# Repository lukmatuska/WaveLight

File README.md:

# WaveLight

A gesture-controlled night light. Wave your hand over it to turn it on or off,
hold your hand over it to set the flame size, and double-wave to pick a color.
The light is an animated candle flame on WS2812 LEDs. It runs on a Li-ion
battery and sleeps when nobody is around.

- **MCU:** ATtiny416 (4 kB flash, 256 B RAM), internal 16 MHz oscillator
- **Sensor:** ams TMF8801 time-of-flight distance sensor
- **LEDs:** 4× WS2812B-2020 (count is configurable)
- **Firmware:** C, MPLAB XC8 (free license), in [`FW/`](FW/)
- **Hardware:** KiCad project in the repository root

---

## Using it

| Gesture | What it does |
|---|---|
| **Wave** (hand over the sensor and away again, under 0.6 s) | Light on / off. Reacts ~0.5 s after the hand leaves, because it waits to see if a second wave follows |
| **Hold + move** (hand stays over the sensor, then moves) | Flame size: closer = smaller, dimmer embers; farther = bigger, brighter flame. Saved when the hand leaves |
| **Wave, then hold right away** | Turns on, then sets the flame size |
| **Double wave** | Color mode: the light dips briefly. Bring your hand back within 2 s and the color follows its distance. Take the hand away, and after 1 s the light dips again and the color is saved |

**Distances:** hands are detected up to **60 cm**. Size and color are set
between about **6 cm** (closest) and **32 cm** (farthest).

**Colors**, from close to far in color mode:

| Hand distance | ~6 cm | | | | | | | | | ~32 cm |
|---|---|---|---|---|---|---|---|---|---|---|
| Color | red | orange | yellow | green | cyan | blue | magenta | red | warm white (2700 K) | cool white (6500 K) |

So the strip goes once around the color wheel back to red, then into warm
white and cools down to 6500 K. The hotter parts of the flame shift a little
further along the strip, which gives the flame its lighter tips.

### Status signals

| LEDs | Meaning |
|---|---|
| Brief dip to dark and back | Color mode started / ended |
| Magenta for 1 s at power-on | Sensor calibrated and calibration stored (first boot after flashing) |
| Red blinking continuously | Sensor not responding. Retries every ~8 s (watchdog reset) |
| 2 red blinks when turning on | Battery low (< 3.5 V), turns on anyway |
| 3 red blinks, stays off | Battery critical (< 3.3 V). Charge above 3.5 V to use again |

The battery signals only appear if the battery check is enabled (see
[Configuration](#configuration)).

### Things that might surprise you

- **Static objects are learned.** Anything that stays still for 10 s becomes
  background. A hand only counts if it is at least 8 cm closer than the
  background, so you can wave between the lamp and e.g. a shelf. After you
  place or remove something, give it ~10 s to adapt.
- **Placed objects never change the settings.** A hold only adjusts the flame
  once the hand has *moved* 3 cm, and objects don't move.
- **Pulling your hand away doesn't change the setting.** On release the
  value from ~200 ms earlier is kept.
- **Idle:** after 15 s without a hand, whether the light is on or off, the
  sensor slows down (one shorter measurement every 200 ms) to save power. The
  first wave still works, but a very quick flick can be missed. Idle
  measurements are shorter, so a hand near the 60 cm limit may only be
  noticed once it comes a bit closer.

---

## Hardware

### Pinout

| ATtiny416 pin | Function |
|---|---|
| PB3 | WS2812 data (LED strip connector J2; also gate of Q1 for the alternative power LED on J3) |
| PB1 / PB0 | I²C SDA / SCL to the TMF8801 (internal pull-ups, no external resistors fitted) |
| PC0 | TMF8801 INT (open drain, internal pull-up) - wakes the MCU |
| PC1 | TMF8801 EN |
| PB4 / PB2 | TMF8801 GPIO0 / GPIO1 (unused, driven low by the sensor) |
| PA1 | Battery voltage measurement (divider middle) |
| PC3 | Battery divider low side - pulled low only while measuring |
| PA0 | UPDI programming |

### Board

- **Power:** Li-ion battery (J6) → power switch (SW1) → TCR2L LDO → VDD for
  the MCU and sensor. The LED strip runs directly from the battery voltage.
- **Charging:** USB-C (J7) or the jack tip → charger IC (U3, charge current set
  by R3). The charger's battery output is on the switched side of SW1, so the
  battery only charges while the switch is on.
- **3.5 mm jack (J1):** tip = charger input, ring = UPDI, sleeve = GND. It is
  used for programming.
- **J4 / J5:** sensor signal headers (VDD, GPIO0/1, SDA, SCL, INT, EN, GND).
- **JP1:** solder jumper EN → GND (holds the sensor off when closed).
- **Battery divider:** R2 1 MΩ (battery → PA1) and R4 470 kΩ (PA1 → PC3).

### Known hardware limitations

- **No I²C pull-ups.** The internal ones are used and the bus runs at 50 kHz.
  Add 4.7 kΩ to VDD on SDA/SCL in the next revision.
- **The LEDs run straight from the battery.** The WS2812B-2020 is specified
  for 3.3-5.3 V. Below ~3.6 V the green and blue channels may lose current
  (dimmer, redder light), and below 3.3 V the LEDs are out of spec.
- **The sensor dominates standby current** (~3 mA), see
  [Power analysis](#power-analysis). A 300 mAh battery lasts about 3.5 days in
  standby.
- **Sensor range is ~64 cm** with the firmware built into the sensor (see
  [Sensor range](#sensor-range)).

---

## Firmware

### Files

| File | Contents |
|---|---|
| [`main.c`](FW/main.c) | Configuration, startup, main loop, gesture → action mapping, sleep, EEPROM settings |
| [`gesture.h`](FW/gesture.h) | Wave / double wave / hold / tracking detection, background learning |
| [`light.h`](FW/light.h) | Flame animation, colors, fades, gamma correction, auto-off |
| [`tmf8801.h`](FW/tmf8801.h) | TMF8801 driver: power-up, factory calibration, measurement, results |
| [`battery.h`](FW/battery.h) | Battery voltage check (ADC) |
| [`twi.h`](FW/twi.h) | I²C master driver |
| [`ws2812b.h`](FW/ws2812b.h) | Cycle-counted WS2812 driver (16 MHz) |
| [`PATCHING.md`](FW/PATCHING.md) | How to upload the TMF8801 RAM patch after switching to an ATtiny1616 |

### Building and flashing

1. Open `FW/` in VS Code with the MPLAB extensions (project file
   `FW/.vscode/Wavelight-firmware.mplab.json`, XC8 v3.00, `ATtiny_DFP` 3.4.278).
2. Build. The optimization level in the project doesn't matter: `main.c`
   forces `-O2` without inlining with a `#pragma`. At `-O0` the firmware
   doesn't fit. The free XC8 license allows `-O2` but not `-Os`.
3. Flash over UPDI (the project uses an MPLAB Snap).
4. **Set the fuse `OSCCFG` to 16 MHz** (`FREQSEL_16MHZ`) on every new chip.
   The factory default is 20 MHz, and then all timing (LED data, I²C, gestures)
   is off by 25%.
5. **First boot after flashing:** keep nothing within 40 cm of the sensor,
   ideally in the dark. The sensor calibrates itself and stores the result
   (1 s magenta flash).

Flashing erases the EEPROM, which holds the sensor calibration and the saved size
and color, unless the `EESAVE` fuse is set.

Flash usage is about 3.65 kB, or 3.9 kB with the battery check, out of 4 kB.

### Configuration

All settings are `#define`s.

**[`main.c`](FW/main.c)**

| Define | Default | Meaning |
|---|---|---|
| `DEBUG_DISTANCE` | 0 | 1 = show the raw distance on the LEDs instead of the night light (see [Debug mode](#debug-mode)) |
| `BATTERY_CHECK` | 0 | 1 = battery divider is fitted, enable the battery check |
| `LED_COUNT` | 4 | Number of WS2812 LEDs (~5 bytes RAM each, up to ~40) |
| `TICK_MS` | 10 | Main loop period |
| `ADJUST_NEAR_MM` | 60 | Hand distance for the smallest flame / first color. +1 step per mm up to 255 steps (~32 cm) |
| `TONE_MODE_WAIT_MS` | 2000 | Time to bring the hand back after a double wave |
| `TONE_MODE_END_MS` | 1000 | Color mode ends this long after the hand left |
| `BATTERY_PERIOD_MS` | 60000 | Battery check interval while running |
| `SENSOR_ACTIVE_MS` | 33 | Sensor measurement period while a hand is around |
| `SENSOR_ACTIVE_KITER` | 900 | Sensor iterations (thousands) per measurement while active |
| `SENSOR_IDLE_MS` | 200 | Sensor measurement period while idle (max 255). Longer = less power, more missed flicks |
| `SENSOR_IDLE_KITER` | 600 | Iterations while idle. Fewer = less power per measurement, maybe less range |
| `IDLE_AFTER_MS` | 15000 | No hand this long → sensor idle (light on or off) |

**[`gesture.h`](FW/gesture.h)**

| Define | Default | Meaning |
|---|---|---|
| `GESTURE_NEAR_MM` | 600 | Maximum hand distance |
| `GESTURE_DROPOUT` | 2 | Missed readings in a row before a hand counts as gone (bridges glitches near the range limit) |
| `GESTURE_BG_MARGIN_MM` | 80 | A hand must be this much closer than the background |
| `GESTURE_BG_TOL_MM` | 30 | Readings within this count as "not moving" |
| `GESTURE_BG_LEARN_MS` | 10000 | Static this long → becomes background |
| `GESTURE_WAVE_MIN_MS` | 50 | Shorter presence = noise |
| `GESTURE_WAVE_MAX_MS` | 600 | Longer presence = hold. Raise it if your waves are slow |
| `GESTURE_DOUBLE_GAP_MS` | 500 | Maximum pause between the two waves of a double wave |
| `GESTURE_HOLD_MOVE_MM` | 30 | A hold only adjusts after the hand moved this much |
| `GESTURE_HISTORY` | 6 | Readings (~200 ms) rolled back when the hand leaves |

**[`light.h`](FW/light.h)**

| Define | Default | Meaning |
|---|---|---|
| `LIGHT_FADE_ON_MS` / `LIGHT_FADE_OFF_MS` | 800 / 1500 | Fade times |
| `LIGHT_AUTO_OFF_MIN` | 0 | Turn off after this many minutes, 0 = never |
| `LIGHT_DEFAULT_BRIGHTNESS` | 255 | Flame size before anything is saved |
| `LIGHT_MIN_BRIGHTNESS` | 24 | Smallest flame size |
| `LIGHT_DEFAULT_TONE` | 0 | Color before anything is saved (0 = red-orange flame). ~10 gives a more orange flame |
| `LIGHT_WB_G` / `LIGHT_WB_B` | 176 / 240 | White balance: WS2812 green and blue are much stronger than red. Tune until the 4000 K white looks neutral |
| `FLAME_SPREAD` | 110 | How much the flame flickers above its base heat |
| `FLAME_CHANGE` | 40 | How often the flicker changes (chance per tick, of 256) |
| `FLAME_GUST` | 2 | How often the whole flame dips (chance per tick, of 256) |
| `FLAME_SPEED` | 2 | Smoothing; higher = calmer flame |
| `FLAME_HUE_SHIFT` | 24 | How much hotter parts shift along the color strip |
| `LIGHT_WHEEL_END` | 192 | Where the color wheel ends and the white strip starts |

**[`battery.h`](FW/battery.h)**

| Define | Default | Meaning |
|---|---|---|
| `BATTERY_LOW_MV` | 3500 | Warn when turning on |
| `BATTERY_CRITICAL_MV` | 3300 | Refuse to turn on / turn off. Cleared above `BATTERY_LOW_MV` |
| `BATTERY_R_TOP` / `BATTERY_R_BOTTOM` | 1000 / 470 | Divider resistors in kΩ |

### How it works

**Sensor.** The TMF8801 runs the measurement app built into its ROM. No
firmware is uploaded, because the ~11 kB patch doesn't fit in 4 kB.
On the first boot the sensor runs its factory calibration (crosstalk). The
14-byte result is stored in EEPROM and sent to the sensor on every start.
It measures with 900k iterations; each measurement takes ~27 ms.

**Gestures.** Every sensor result goes into `gesture_reading()`, which
decides whether a hand is present. `gesture_update()` runs every 10 ms and
turns presence over time into events: wave, double wave, hold, hold end,
track, track end. While color mode is active, wave and hold detection are off
and the hand position is reported directly ("tracking"). When color mode ends,
a hand that is still there is ignored until it leaves, so color mode never
turns into a size change.

**Light.** The output level fades linearly in perceptual brightness and is
gamma-corrected, so fades look even. Each LED has a "heat" value that
drifts towards random targets. Neighboring LEDs are coupled, so the flicker
travels along the strip, and occasionally the whole flame dips (a gust).
Heat sets both the brightness and a small color shift. The size setting moves
the base heat up and down.

**Power.** While a hand is around, the sensor measures every 33 ms with 900k
iterations. After `IDLE_AFTER_MS` with no hand, no gesture pending and no
color mode, **whether the light is on or off**, the sensor switches to
`SENSOR_IDLE_MS` / `SENSOR_IDLE_KITER` (200 ms, 600k) and goes to standby
between measurements. A hand switches it back.

What the MCU does then depends on the light:
- **Light on (or fading):** the MCU stays awake and runs the flame every 10 ms.
- **Light off:** the MCU goes to power-down and is woken by the sensor's INT
  pin, which goes low on every result (the TMF8801 has no distance-threshold
  interrupt). After each wake, the firmware catches up the missed 10 ms ticks
  so all timing stays correct, then sleeps again unless a hand was seen.

Unused pins have their digital inputs disabled, and the battery divider only
draws current during a measurement. A watchdog (~8 s, also running in sleep)
resets the device if the sensor ever stops waking it.

For the resulting currents and battery life, see [Power analysis](#power-analysis).

**Settings.** The flame size and color are saved to EEPROM when a hold or
color mode ends, and only if they changed. EEPROM layout: page 0 =
calibration + marker, page 1 = size, color + marker.

### Debug mode

Set `DEBUG_DISTANCE 1` to show what the sensor sees, at 10 cm resolution:

- **Color = 40 cm band:** green 0-40, yellow 40-80, red 80-120,
  magenta 120-160, white over 160 cm
- **Number of lit LEDs = 10 cm steps within the band** (1-4). For example,
  3 yellow = 60-70 cm.
- **First LED blue:** the sensor reports no object
- **All cyan:** no new reading for 0.5 s

The display assumes 4 LEDs.

### Sensor range

With the ROM firmware, the TMF8801 here reports "no object" beyond ~64 cm,
even for a white wall in the dark with calibration. The datasheet only
promises its 2.5 m range with the latest ams RAM patch (~11 kB, uploaded
on every boot) and a tuned oscillator. An ATtiny1616 (16 kB) in the same
package fits the patch. The steps are in [`FW/PATCHING.md`](FW/PATCHING.md).

---

## Power analysis

Estimates for 4× WS2812B-2020 and a **300 mAh** Li-ion battery. They are
calculated from datasheet values and a simulation of the flame code. **Nothing
has been measured yet.**

### Assumptions

- **Usable capacity 270 mAh:** about 90% of 300 mAh, from 4.2 V down to the
  3.3 V cut-off.
- **Battery current = load current.** The LDO is linear, and the LEDs are
  constant-current drivers. This holds while the battery is high enough for
  the green/blue LED channels (~3.6 V); below that the LEDs draw less and get
  dimmer.
- **Room temperature, typical (not maximum) values.**
- **Default firmware settings:** sensor every 33 ms with 900k iterations
  while a hand is around, every 200 ms with 600k iterations while idle; MCU at
  16 MHz.
- **The iteration count really changes the measurement time.** The datasheet
  contradicts itself on the byte order, and the firmware follows the register
  description. **Verify by measuring the standby current with
  `SENSOR_IDLE_KITER` 600 vs 900.** It should drop by about a third; if it
  doesn't, the byte order is wrong.

### Per component

| Component | State | Current | Source |
|---|---|---|---|
| TMF8801 | active: every 33 ms, 900k (hand around, or < 15 s after) | ~27 mA | DS000648: 27 mA average at 30 Hz, 900k iterations |
| TMF8801 | idle: every 200 ms, 600k | **~3.0 mA** | DS000648: 17.7 mA at 30 Hz with 600k → ~0.59 mC per measurement; + 85 µA standby in between |
| ATtiny416 | awake, 16 MHz, ~3 V (light on) | ~3 mA | datasheet fig. 36-1 |
| ATtiny416 | light off, idle: power-down + ~6 ms awake per wake-up (I²C, catch-up ticks) | ~0.1 mA | 3% of 3 mA; power-down itself ~0.2 µA (fig. 36-9) |
| WS2812B-2020 ×4 | dark | ≤ 4 µA | V6 datasheet: quiescent ≤ 1 µA each |
| WS2812B-2020 ×4 | flame | 3-71 mA average, see below | 12 mA per channel at full, flame simulated |
| LDO, charger, watchdog, divider, pull-ups | always | a few µA | negligible |

### LED current of the flame

These figures come from simulating the actual `light.h` algorithm (random
generator, heat model, colors, white balance) for 10 minutes. Each LED channel
draws 12 mA × PWM / 255.

| Color | Size 255 | Size 160 | Size 80 | Size 24 (min) |
|---|---|---|---|---|
| Red (default) | 31.5 mA | 15.6 mA | 6.9 mA | 3.1 mA |
| Orange | 44.4 mA | 21.3 mA | 9.1 mA | 4.0 mA |
| Yellow | 28.6 mA | 17.3 mA | 9.1 mA | 4.6 mA |
| Blue | 30.5 mA | 14.9 mA | 6.6 mA | 3.0 mA |
| Warm white 2700 K | 41.2 mA | 21.1 mA | 9.5 mA | 4.3 mA |
| Cool white 6500 K | 71.4 mA | 37.6 mA | 17.4 mA | 8.1 mA |

- **Peak:** about 108 mA for the LEDs (cool white, size 255, during flicker
  peaks), so ~140 mA in total. This is under 0.5 C for a 300 mAh cell.
- **Theoretical maximum:** 4 × 36 mA = 144 mA; the flame never gets there.

### Total current and run time (270 mAh usable)

After the first 15 s without a hand, the light runs with the sensor idle. The
"on" rows assume that; the active state only applies briefly after each
interaction.

| Scenario | Sensor | MCU | LEDs | Total | Run time |
|---|---|---|---|---|---|
| **Standby** (light off, idle) | 3.0 | 0.1 | 0 | **3.1 mA** | **~87 h (3.6 days)** |
| Hand around / < 15 s after (light off) | 27 | 3 | 0 | 30 mA | (short) |
| On: red, size 24 | 3.0 | 3 | 3.1 | 9.1 mA | 30 h |
| On: red, size 80 | 3.0 | 3 | 6.9 | 12.9 mA | 21 h |
| On: red, size 160 | 3.0 | 3 | 15.6 | 21.6 mA | 12.5 h |
| On: red, size 255 (default) | 3.0 | 3 | 31.5 | 37.5 mA | 7.2 h |
| On: warm white, size 255 | 3.0 | 3 | 41.2 | 47.2 mA | 5.7 h |
| On: cool white, size 255 | 3.0 | 3 | 71.4 | 77.4 mA | 3.5 h |

**Example day:** the light is on for 30 min (red, size 160) and the rest is
standby. That's 11 mAh + 73 mAh = **~84 mAh per day, so a charge lasts about
3 days.**

Before the sensor idled while on and used fewer iterations (100 ms / 900k idle,
33 ms whenever on), standby was 9.3 mA (~29 h) and red at size 160 ran 5.9 h.

### Findings

1. **Standby is still mostly the sensor** (3.0 of 3.1 mA). Each measurement
   costs a fixed charge (~0.59 mC at 600k), so the average current scales
   with measurement interval and iteration count.
2. **While the light is on, the MCU is now a big share.** At small sizes the
   busy 16 MHz loop (3 mA) costs as much as the sensor or the LEDs.
3. **The LEDs cost nothing when dark** (WS2812B-2020 V6: ≤ 1 µA). Older
   WS2812B revisions and clones draw ~0.5-1 mA each, so check the part
   revision if standby measures higher than expected.

### Ways to extend run time further (not implemented)

| Change | Effect | Cost |
|---|---|---|
| Idle sleep instead of busy-waiting between 10 ms ticks while on (MCU ~1 mA instead of 3 mA) | red, size 24: 30 → ~38 h | small code change |
| Fewer idle iterations (e.g. 400k) | standby roughly -30% | idle range shrinks further (untested) |
| Power switch off when not in use | ~0 mA | the battery doesn't charge while switched off (see [Board](#board)) |

---

## References

- TMF8801 datasheet DS000648 v7-00 (ams OSRAM): register map, commands,
  bootloader protocol, calibration
- [WS2812B-2020 V6 datasheet](https://www.tme.com/Document/f57342b0dc3e7d573aa1f8b6b5942fcf/WS2812B-2020-V6_V1.2_EN.pdf)
  (WorldSemi): quiescent current, channel current, supply range, reset time
- [ATtiny416/417/814/816/817 datasheet](https://cdn.sparkfun.com/assets/e/e/4/c/8/ATtiny817-datasheet.pdf):
  active and power-down supply current (figures 36-1, 36-9)
- [SparkFun TMF8801 Arduino library](https://github.com/sparkfun/SparkFun_TMF8801_Arduino_Library)
  and [DFRobot TMF8x01 library](https://github.com/DFRobot/DFRobot_TMF8x01):
  measurement command bytes, calibration flow, RAM patch data

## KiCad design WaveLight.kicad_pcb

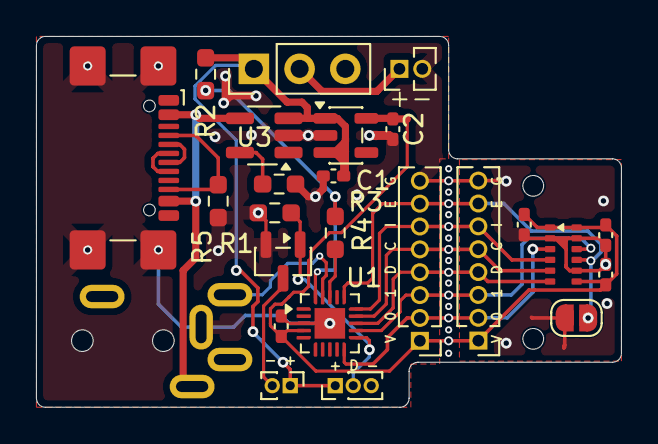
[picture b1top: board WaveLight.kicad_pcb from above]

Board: 2 copper layers, 32.5 x 20.6 mm, 25 parts (1 on the bottom side), 20 nets.

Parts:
C1, C2: 100n; C_0402_1005Metric_Pad0.74x0.62mm_HandSolder
C3, C4, C5, C6: 0.1u; C_0402_1005Metric_Pad0.74x0.62mm_HandSolder
J1: AudioJack4_SwitchT1; ASJ-190-A
J2: Ledstrip_conn; PinHeader_1x03_P1.00mm_Vertical
J3: PowerLED_conn; PinHeader_1x02_P1.00mm_Vertical
J4, J5: Conn_01x08_Pin; PinHeader_1x08_P1.27mm_Vertical
J6: Batt; PinHeader_1x02_P1.27mm_Vertical
J7: USB_C_Receptacle_USB2.0_14P; USB_C_Receptacle_GCT_USB4110
JP1: SolderJumper_2_Open; SolderJumper-2_P1.3mm_Open_RoundedPad1.0x1.5mm
Q1: AO3400A or similar; SOT-23
R1: 10k; R_0603_1608Metric_Pad0.98x0.95mm_HandSolder
R2: 1M; R_0603_1608Metric_Pad0.98x0.95mm_HandSolder
R3: CH_PROG; R_0603_1608Metric_Pad0.98x0.95mm_HandSolder
R4: 470K; R_0603_1608Metric_Pad0.98x0.95mm_HandSolder
R5: 56k; R_0603_1608Metric_Pad0.98x0.95mm_HandSolder
SW1: POWER_SW_SPDT; PinHeader_1x03_P2.54mm_Vertical
TCR2Lx1: TCR2Lx1; SOT-23-5
U1: ATtiny416-M; VQFN-20-1EP_3x3mm_P0.4mm_EP1.7x1.7mm
U2: TMF8801
U3: TP charger; SOT-23-5_HandSoldering

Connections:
/BV_GND: R4.2, U1.18 (PC3)
/BV_meas: R2.2, R4.1, U1.20 (PA1)
/DM: J7.A7 (D-), J7.B7 (D-)
/DP: J7.A6 (D+), J7.B6 (D+)
/EN: J4.7, J5.7, JP1.2 (B), U1.16 (PC1), U2.9 (EN)
/GP0: J4.2, J5.2, U1.10 (PB4), U2.3 (GPIO0)
/GP1: J4.3, J5.3, U1.12 (PB2), U2.10 (GPIO1)
/INT: J4.6, J5.6, U1.15 (PC0), U2.4 (INT)
/SCL: J4.5, J5.5, U1.14 (PB0), U2.5 (SCL)
/SDA: J4.4, J5.4, U1.13 (PB1), U2.6 (SDA)
/UPDI: J1.R1, U1.19 (~RESET/PA0)
/led_RGB: J2.2, Q1.1 (G), R1.1, U1.11 (PB3)
GND: C1.2, C2.2, C3.2, C4.2, C5.2, C6.2, J1.S, J2.3, J4.8, J5.8, J6.2, J7.A1 (GND), J7.A12 (GND), J7.B1 (GND), J7.B12 (GND), J7.S1 (SHIELD), JP1.1 (A), Q1.2 (S), R1.2, R3.2, R5.2, TCR2Lx1.2 (GND), U1.3 (GND), U1.21 (GND), U2.2 (GNDC), U2.8 (GND), U2.11 (GND), U3.2 (GND)
unnamed: J3.2, Q1.3 (D)
unnamed: J6.1, SW1.2 (B)
unnamed: J7.A5 (CC1), J7.B5 (CC2), R5.1
unnamed: R3.1, U3.5 (PROG)
VBUS: C1.1, J2.1, J3.1, R2.1, SW1.1 (A), TCR2Lx1.1 (Vin), TCR2Lx1.3 (Control), U3.3 (BAT)
VDC: J1.T, J7.A4 (VBUS), J7.A9 (VBUS), J7.B4 (VBUS), J7.B9 (VBUS), U3.4 (Vcc)
VDD: C2.1, C3.1, C4.1, C5.1, C6.1, J4.1, J5.1, TCR2Lx1.5 (Vout), U1.4 (VCC), U2.1 (VDDC), U2.7 (VDD), U2.12 (VDDV)

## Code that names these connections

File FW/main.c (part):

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 * @details Hardware overview:
 * - Attiny416
 * - no external clock
 * - 4x WS2812b LED on pin PB3
 * - TMF8801 Distance Sensor:
 *   - SDA: PB1
 *   - SCL: PB0
 *   - INT: PC0
 *   - EN: PC1
 *   - GPIO0: PB4
 *   - GPIO1: PB2
 * - Battery divider 1M / 470k: measure PA1, low side PC3
 *
 * Requires fuse OSCCFG = 16 MHz (FREQSEL_16MHZ), factory default is 20 MHz.
 *
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 */
static void pins_init(void) {
    for (uint8_t i = 2; i < 8; i++) (&PORTA.PIN0CTRL)[i] = PORT_ISC_INPUT_DISABLE_gc;  // PA2-PA7 n.c.
    PORTB.PIN2CTRL = PORT_ISC_INPUT_DISABLE_gc;  // sensor GPIO1
    PORTB.PIN4CTRL = PORT_ISC_INPUT_DISABLE_gc;  // sensor GPIO0
    PORTB.PIN5CTRL = PORT_ISC_INPUT_DISABLE_gc;  // n.c.
    PORTC.PIN2CTRL = PORT_ISC_INPUT_DISABLE_gc;  // n.c.
#if !BATTERY_CHECK
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 */
static void sleep_until_sensor(void) {
    cli();
    PORTC.PIN0CTRL = PORT_PULLUPEN_bm | PORT_ISC_LEVEL_gc;  // PC0 isn't async, level works in power-down
    SLPCTRL.CTRLA = SLPCTRL_SMODE_PDOWN_gc | SLPCTRL_SEN_bm;
    sei();
    asm volatile("sleep");  // runs before a pending interrupt, so no wakeup is lost
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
